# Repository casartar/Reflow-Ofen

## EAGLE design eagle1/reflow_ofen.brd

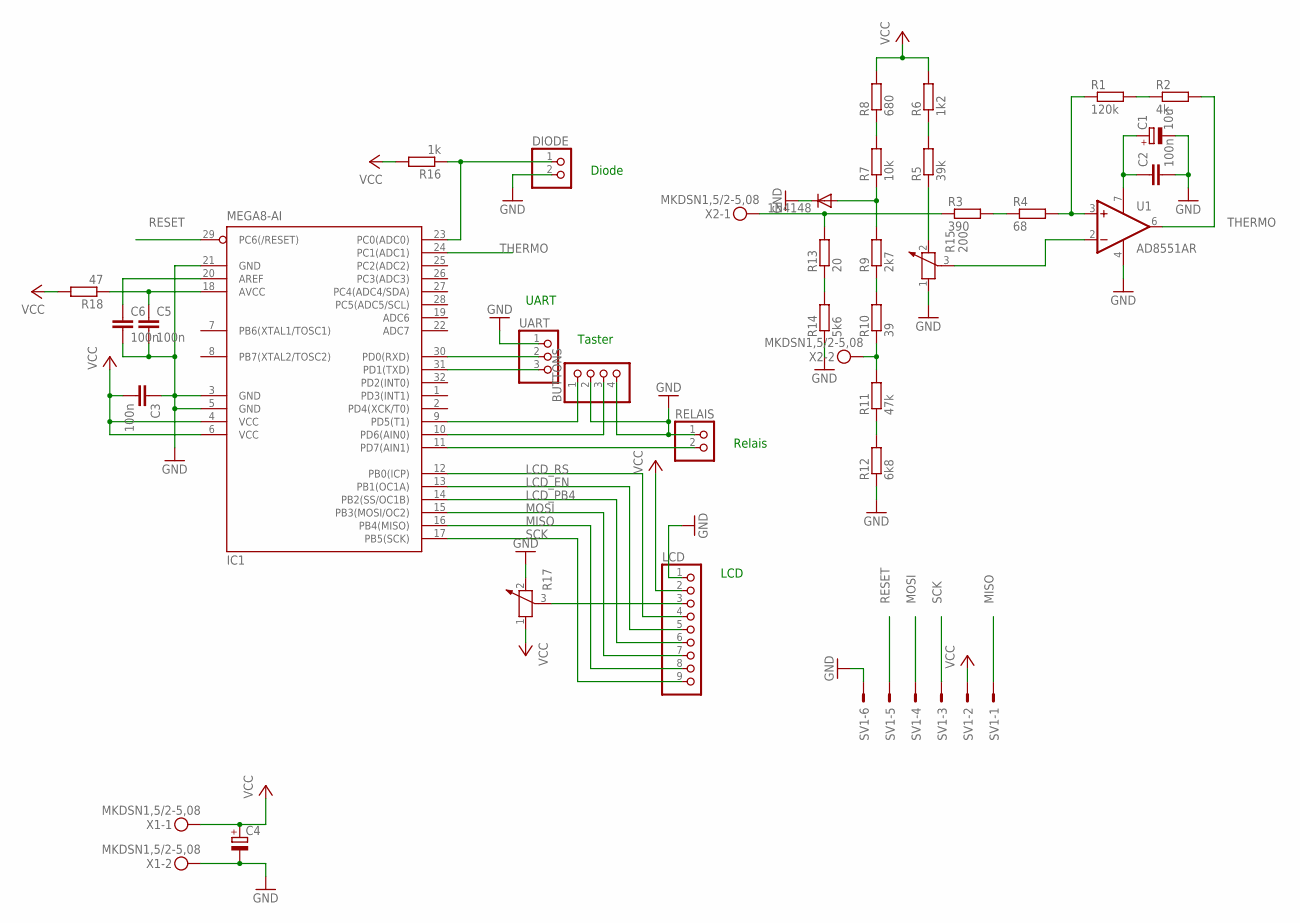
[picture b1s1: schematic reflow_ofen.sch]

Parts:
1N4148: DIODE-SOD80C; SOD80C
BUTTONS: PINHD-1X4; 1X04
C1: 10u; 153CLV-0405
C2, C3, C5, C6: 100n; C0805
C4: CPOL-EU153CLV-0505; 153CLV-0505
DIODE: PINHD-1X2; 1X02
IC1: MEGA8-AI; TQFP32-08
LCD: PINHD-1X9; 1X09
R1: 120k; R0805
R2: 4k; R0805
R3: 390; R0805
R4: 68; R0805
R5: 39k; R0805
R6: 1k2; R0805
R7: 10k; R0805
R8: 680; R0805
R9: 2k7; R0805
R10: 39; R0805
R11: 47k; R0805
R12: 6k8; R0805
R13: 20; R0805
R14: 5k6; R0805
R15: 200; PT-10
R16: 1k; R0805
R17: POTENTIOMETER_PT-10; PT-10
R18: 47; R0805
RELAIS: PINHD-1X2; 1X02
SV1: ML6E; ML6
U1: AD8551AR; SO8
UART: PINHD-1X3; 1X03
X1, X2: MKDSN1,5/2-5,08

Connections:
GND: 1N4148.C, BUTTONS.2, BUTTONS.4, C1.-, C2.2, C3.1, C4.-, C5.2, C6.2, DIODE.2, IC1.3 (GND), IC1.5 (GND), IC1.21 (GND), LCD.1, R12.1, R14.1, R15.1, R17.2, RELAIS.1, SV1.6, U1.4 (GND), UART.1, X1.2
LCD_EN: IC1.13 (PB1(OC1A)), LCD.5
LCD_PB4: IC1.14 (PB2(SS/OC1B)), LCD.6
LCD_RS: IC1.12 (PB0(ICP)), LCD.4
MISO: IC1.16 (PB4(MISO)), LCD.8, SV1.1
MOSI: IC1.15 (PB3(MOSI/OC2)), LCD.7, SV1.4
unnamed: R1.1, R4.2, U1.3 (+IN)
unnamed: R3.2, R4.1
unnamed: R15.3, U1.2 (-IN)
unnamed: R5.1, R15.2
unnamed: R5.2, R6.1
unnamed: DIODE.1, IC1.23 (PC0(ADC0)), R16.1
unnamed: R7.2, R8.1
unnamed: 1N4148.A, R7.1, R9.2
unnamed: R9.1, R10.2
unnamed: R10.1, R11.2, X2.2
unnamed: R11.1, R12.2
unnamed: R3.1, R13.2, X2.1
unnamed: R13.1, R14.2
unnamed: IC1.31 (PD1(TXD)), UART.3
unnamed: R1.2, R2.1
unnamed: IC1.30 (PD0(RXD)), UART.2
unnamed: C1.+, C2.1, U1.7 (V+)
unnamed: IC1.11 (PD7(AIN1)), RELAIS.2
unnamed: BUTTONS.3, IC1.10 (PD6(AIN0))
unnamed: BUTTONS.1, IC1.9 (PD5(T1))
unnamed: LCD.3, R17.3
unnamed: C5.1, IC1.18 (AVCC), R18.1
unnamed: C6.1, IC1.20 (AREF)
RESET: IC1.29 (PC6(/RESET)), SV1.5
SCK: IC1.17 (PB5(SCK)), LCD.9, SV1.3
THERMO: IC1.24 (PC1(ADC1)), R2.2, U1.6 (OUT)
VCC: C3.2, C4.+, IC1.4 (VCC), IC1.6 (VCC), LCD.2, R6.2, R8.2, R16.2, R17.1, R18.2, SV1.2, X1.1

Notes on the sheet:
Diode
UART
Taster
Relais
LCD

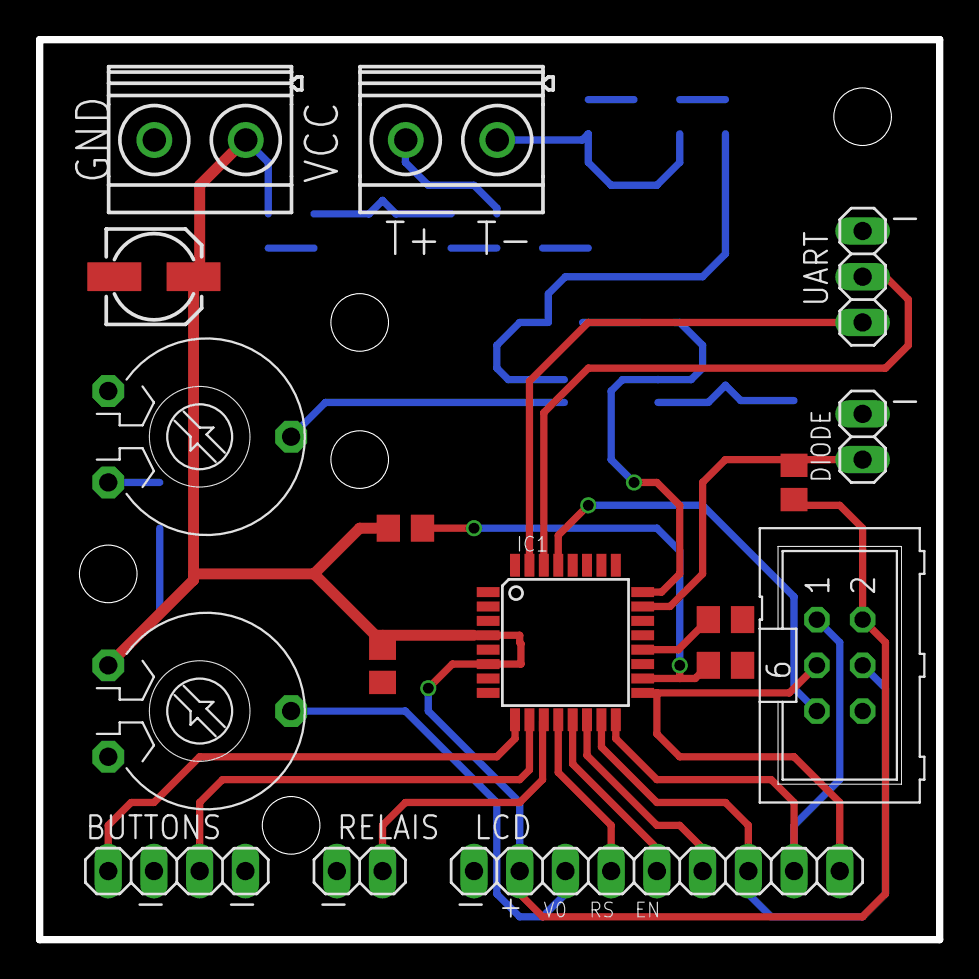
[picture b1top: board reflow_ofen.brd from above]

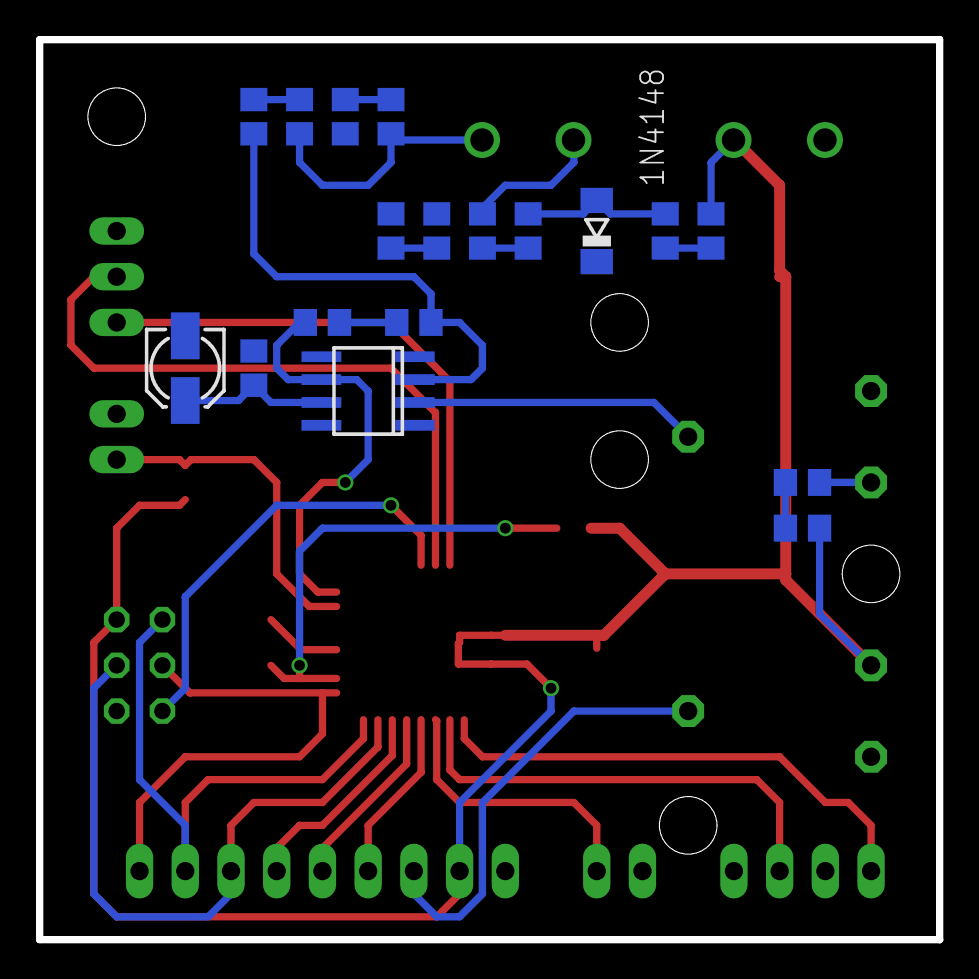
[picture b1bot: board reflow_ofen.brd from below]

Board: 2 copper layers, 50.0 x 50.0 mm, 35 parts (18 on the bottom side), 33 nets.

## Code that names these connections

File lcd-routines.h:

// Ansteuerung eines HD44780 kompatiblen LCD im 4-Bit-Interfacemodus
// http://www.mikrocontroller.net/articles/AVR-GCC-Tutorial/LCD-Ansteuerung
//
 
#ifndef LCD_ROUTINES_H
#define LCD_ROUTINES_H
 
////////////////////////////////////////////////////////////////////////////////
// Hier die verwendete Taktfrequenz in Hz eintragen, wichtig!
 
#ifndef F_CPU
#define F_CPU 1000000UL
#endif
 
////////////////////////////////////////////////////////////////////////////////
// Pinbelegung für das LCD, an verwendete Pins anpassen
// Alle LCD Pins müssen an einem Port angeschlossen sein und die 4
// Datenleitungen müssen auf aufeinanderfolgenden Pins liegen
 
//  LCD DB4-DB7 <-->  PORTD Bit PD0-PD3
#define LCD_PORT      PORTB
#define LCD_DDR       DDRB
#define LCD_DB        PB2
 
//  LCD RS      <-->  PORTD Bit PD4     (RS: 1=Data, 0=Command)
#define LCD_RS        PB0
 
//  LCD EN      <-->  PORTD Bit PD5     (EN: 1-Impuls für Daten)
#define LCD_EN        PB1
 
////////////////////////////////////////////////////////////////////////////////
// LCD Ausführungszeiten (MS=Millisekunden, US=Mikrosekunden)
 
#define LCD_BOOTUP_MS           15
#define LCD_ENABLE_US           20
#define LCD_WRITEDATA_US        46
#define LCD_COMMAND_US          42
 
#define LCD_SOFT_RESET_MS1      5
#define LCD_SOFT_RESET_MS2      1
#define LCD_SOFT_RESET_MS3      1
#define LCD_SET_4BITMODE_MS     5
 
#define LCD_CLEAR_DISPLAY_MS    2
#define LCD_CURSOR_HOME_MS      2
 
////////////////////////////////////////////////////////////////////////////////
// Zeilendefinitionen des verwendeten LCD
// Die Einträge hier sollten für ein LCD mit einer Zeilenlänge von 16 Zeichen passen
// Bei anderen Zeilenlängen müssen diese Einträge angepasst werden
 
#define LCD_DDADR_LINE1         0x00
#define LCD_DDADR_LINE2         0x40
#define LCD_DDADR_LINE3         0x10
#define LCD_DDADR_LINE4         0x50
 
////////////////////////////////////////////////////////////////////////////////
// Initialisierung: muss ganz am Anfang des Programms aufgerufen werden.
void lcd_init( void );
 
////////////////////////////////////////////////////////////////////////////////
// LCD löschen
void lcd_clear( void );
 
////////////////////////////////////////////////////////////////////////////////
// Cursor in die 1. Zeile, 0-te Spalte
void lcd_home( void );
 
////////////////////////////////////////////////////////////////////////////////
// Cursor an eine beliebige Position 
void lcd_setcursor( uint8_t spalte, uint8_t zeile );
 
////////////////////////////////////////////////////////////////////////////////
// Ausgabe eines einzelnen Zeichens an der aktuellen Cursorposition 
void lcd_data( uint8_t data );
 
////////////////////////////////////////////////////////////////////////////////
// Ausgabe eines Strings an der aktuellen Cursorposition 
void lcd_string( const char *data );
 
////////////////////////////////////////////////////////////////////////////////
// Definition eines benutzerdefinierten Sonderzeichens.
// data muss auf ein Array[5] mit den Spaltencodes des zu definierenden Zeichens
// zeigen
void lcd_generatechar( uint8_t code, const uint8_t *data );
 
////////////////////////////////////////////////////////////////////////////////
// Ausgabe eines Kommandos an das LCD.
void lcd_command( uint8_t data );
 
 
////////////////////////////////////////////////////////////////////////////////
// LCD Befehle und Argumente.
// Zur Verwendung in lcd_command
 
// Clear Display -------------- 0b00000001
#define LCD_CLEAR_DISPLAY       0x01
 
// Cursor Home ---------------- 0b0000001x
#define LCD_CURSOR_HOME         0x02
 
// Set Entry Mode ------------- 0b000001xx
#define LCD_SET_ENTRY           0x04
 
#define LCD_ENTRY_DECREASE      0x00
#define LCD_ENTRY_INCREASE      0x02
#define LCD_ENTRY_NOSHIFT       0x00
#define LCD_ENTRY_SHIFT         0x01
 
// Set Display ---------------- 0b00001xxx
#define LCD_SET_DISPLAY         0x08
 
#define LCD_DISPLAY_OFF         0x00
#define LCD_DISPLAY_ON          0x04
#define LCD_CURSOR_OFF          0x00
#define LCD_CURSOR_ON           0x02
#define LCD_BLINKING_OFF        0x00
#define LCD_BLINKING_ON         0x01
 
// Set Shift ------------------ 0b0001xxxx
#define LCD_SET_SHIFT           0x10
 
#define LCD_CURSOR_MOVE         0x00
#define LCD_DISPLAY_SHIFT       0x08
#define LCD_SHIFT_LEFT          0x00
#define LCD_SHIFT_RIGHT         0x04
 
// Set Function --------------- 0b001xxxxx
#define LCD_SET_FUNCTION        0x20
 
#define LCD_FUNCTION_4BIT       0x00
#define LCD_FUNCTION_8BIT       0x10
#define LCD_FUNCTION_1LINE      0x00
#define LCD_FUNCTION_2LINE      0x08
#define LCD_FUNCTION_5X7        0x00
#define LCD_FUNCTION_5X10       0x04
 
#define LCD_SOFT_RESET          0x30
 
// Set CG RAM Address --------- 0b01xxxxxx  (Character Generator RAM)
#define LCD_SET_CGADR           0x40
 
#define LCD_GC_CHAR0            0
#define LCD_GC_CHAR1            1
#define LCD_GC_CHAR2            2
#define LCD_GC_CHAR3            3
#define LCD_GC_CHAR4            4
#define LCD_GC_CHAR5            5
#define LCD_GC_CHAR6            6
#define LCD_GC_CHAR7            7
 
// Set DD RAM Address --------- 0b1xxxxxxx  (Display Data RAM)
#define LCD_SET_DDADR           0x80
 
#endif 

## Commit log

2015-04-26 All functions included
2015-05-26 eagle
2022-12-31 prevent corrupted lcd data by init it cyclic
